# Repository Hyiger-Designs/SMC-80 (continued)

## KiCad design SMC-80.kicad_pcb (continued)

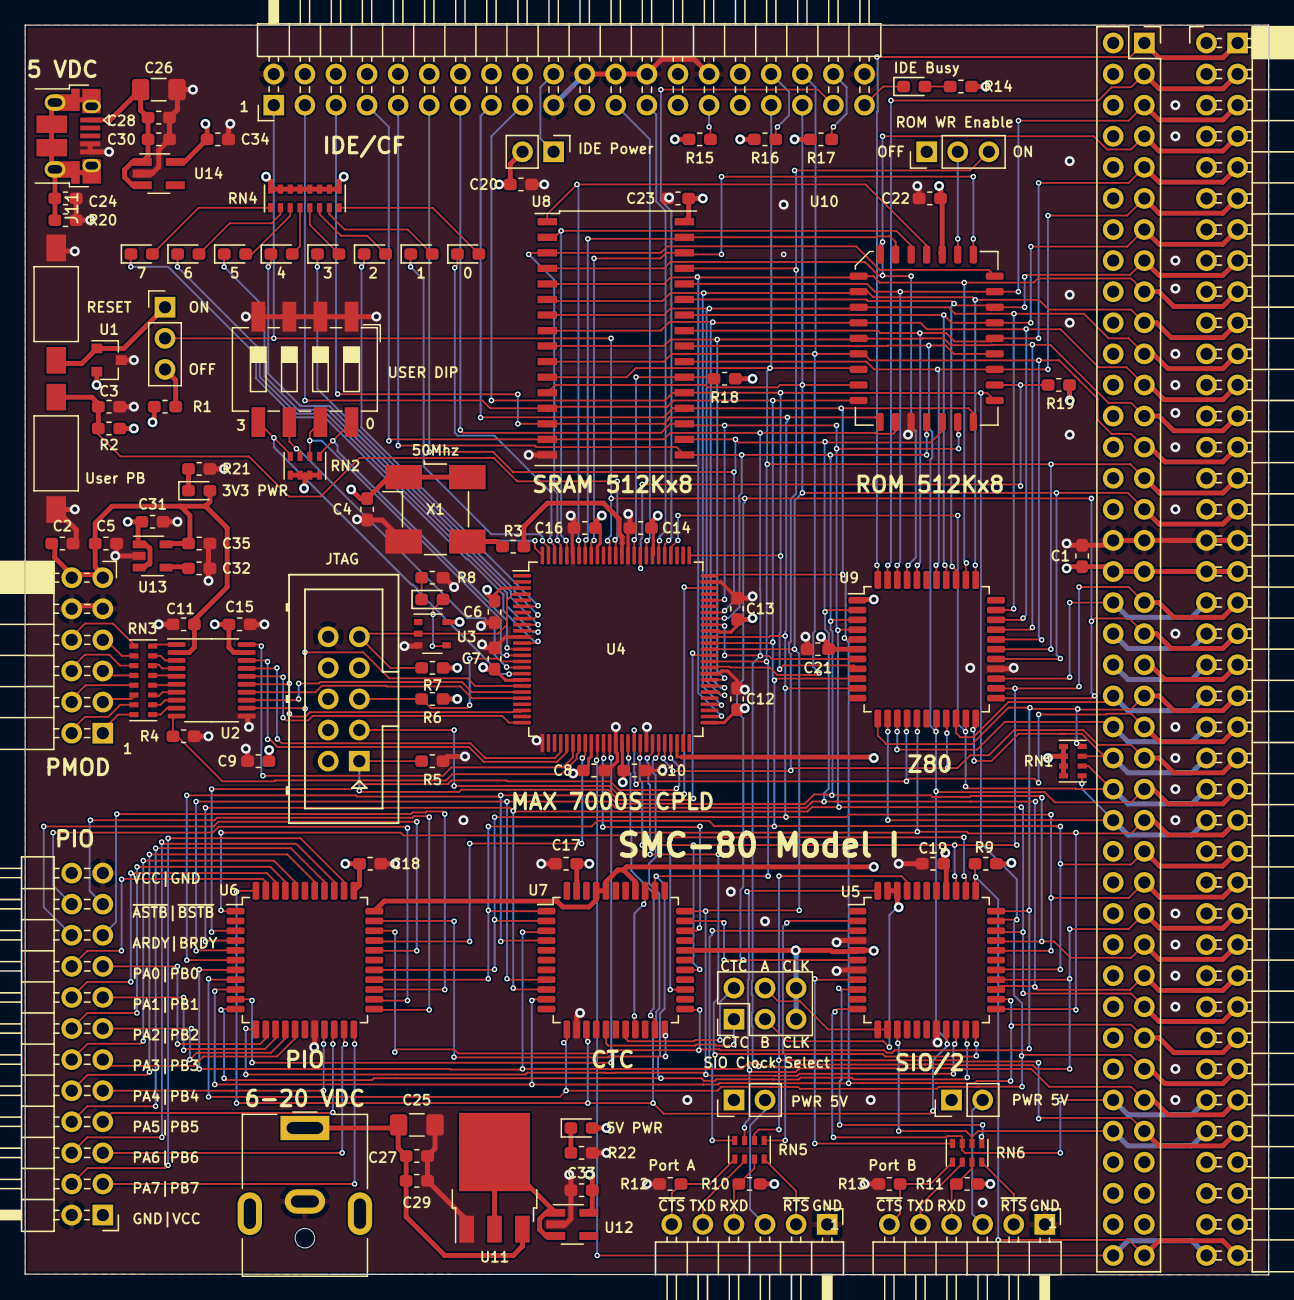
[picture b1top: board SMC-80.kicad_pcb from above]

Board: 4 copper layers, 101.6 x 102.1 mm, 109 parts (0 on the bottom side), 174 nets.

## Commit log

2020-04-18 Initial version
2020-04-18 Renamed to SMC-80
2020-04-18 trace routing
2020-04-19 Routing finished
2020-04-19 reorganized sheets, added SIO clk select
2020-04-19 remove old files, added jtag pullup
2020-04-20 Changed 5V regulator, added additional SS text
2020-05-07 added 5M160ZE64C4N
